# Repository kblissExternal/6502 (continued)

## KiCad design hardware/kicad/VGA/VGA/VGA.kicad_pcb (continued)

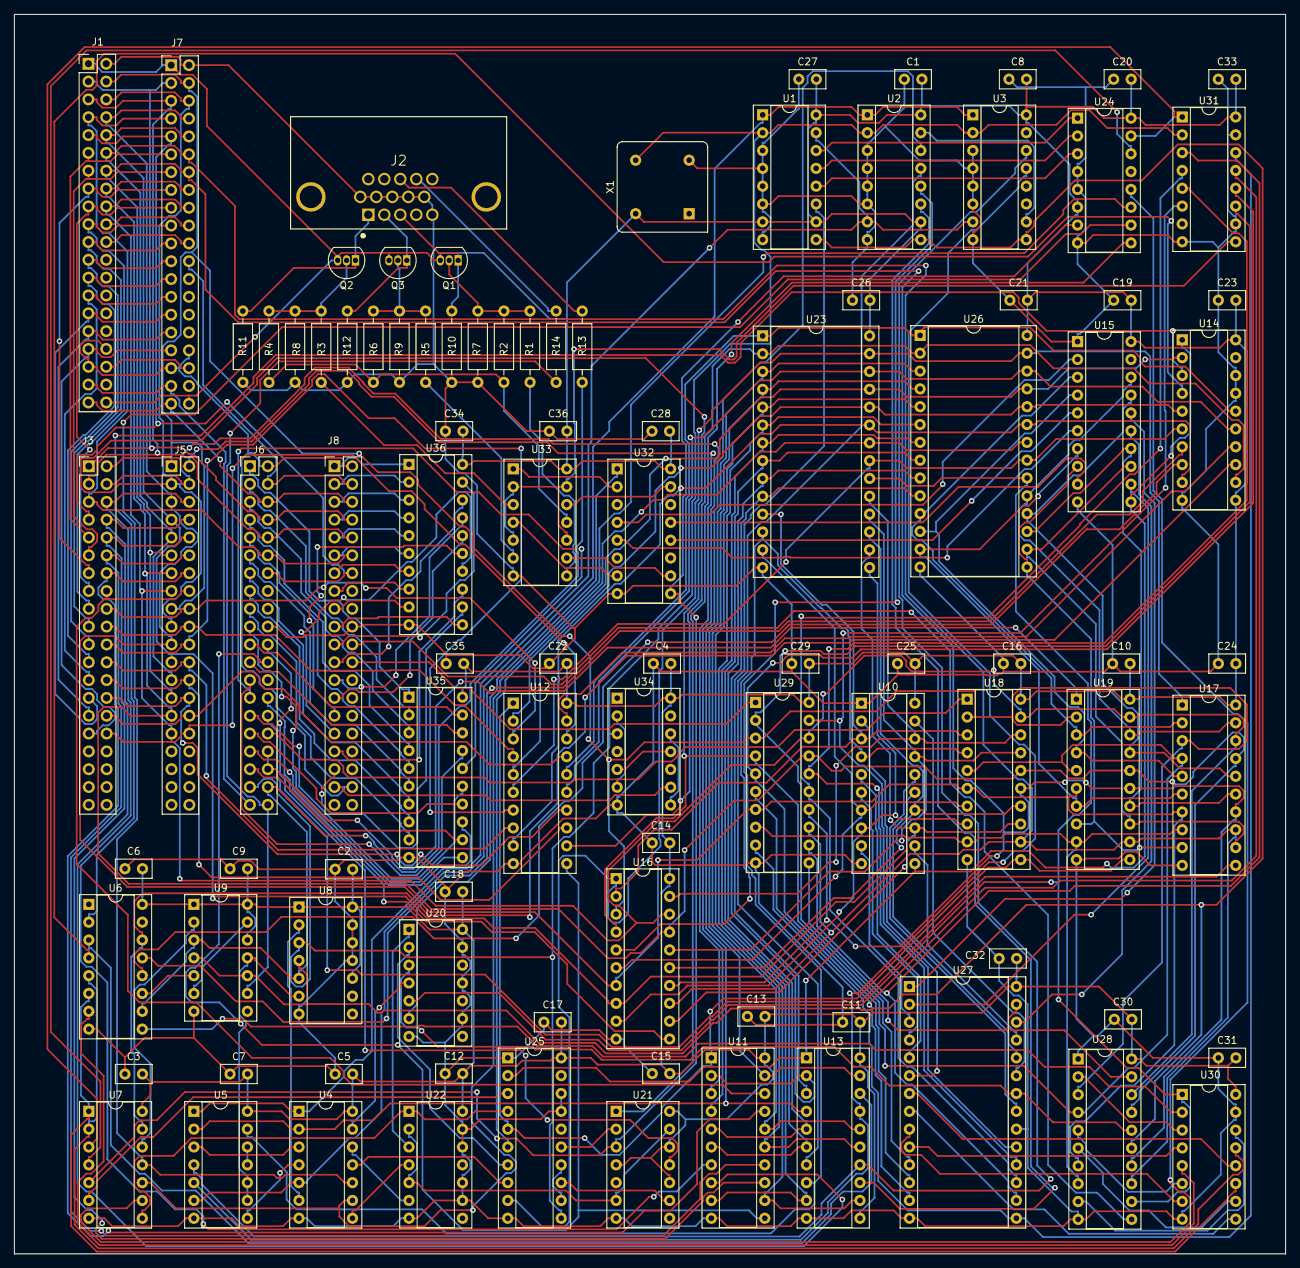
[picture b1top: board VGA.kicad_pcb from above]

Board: 2 copper layers, 181.2 x 176.6 mm, 97 parts (0 on the bottom side), 239 nets.

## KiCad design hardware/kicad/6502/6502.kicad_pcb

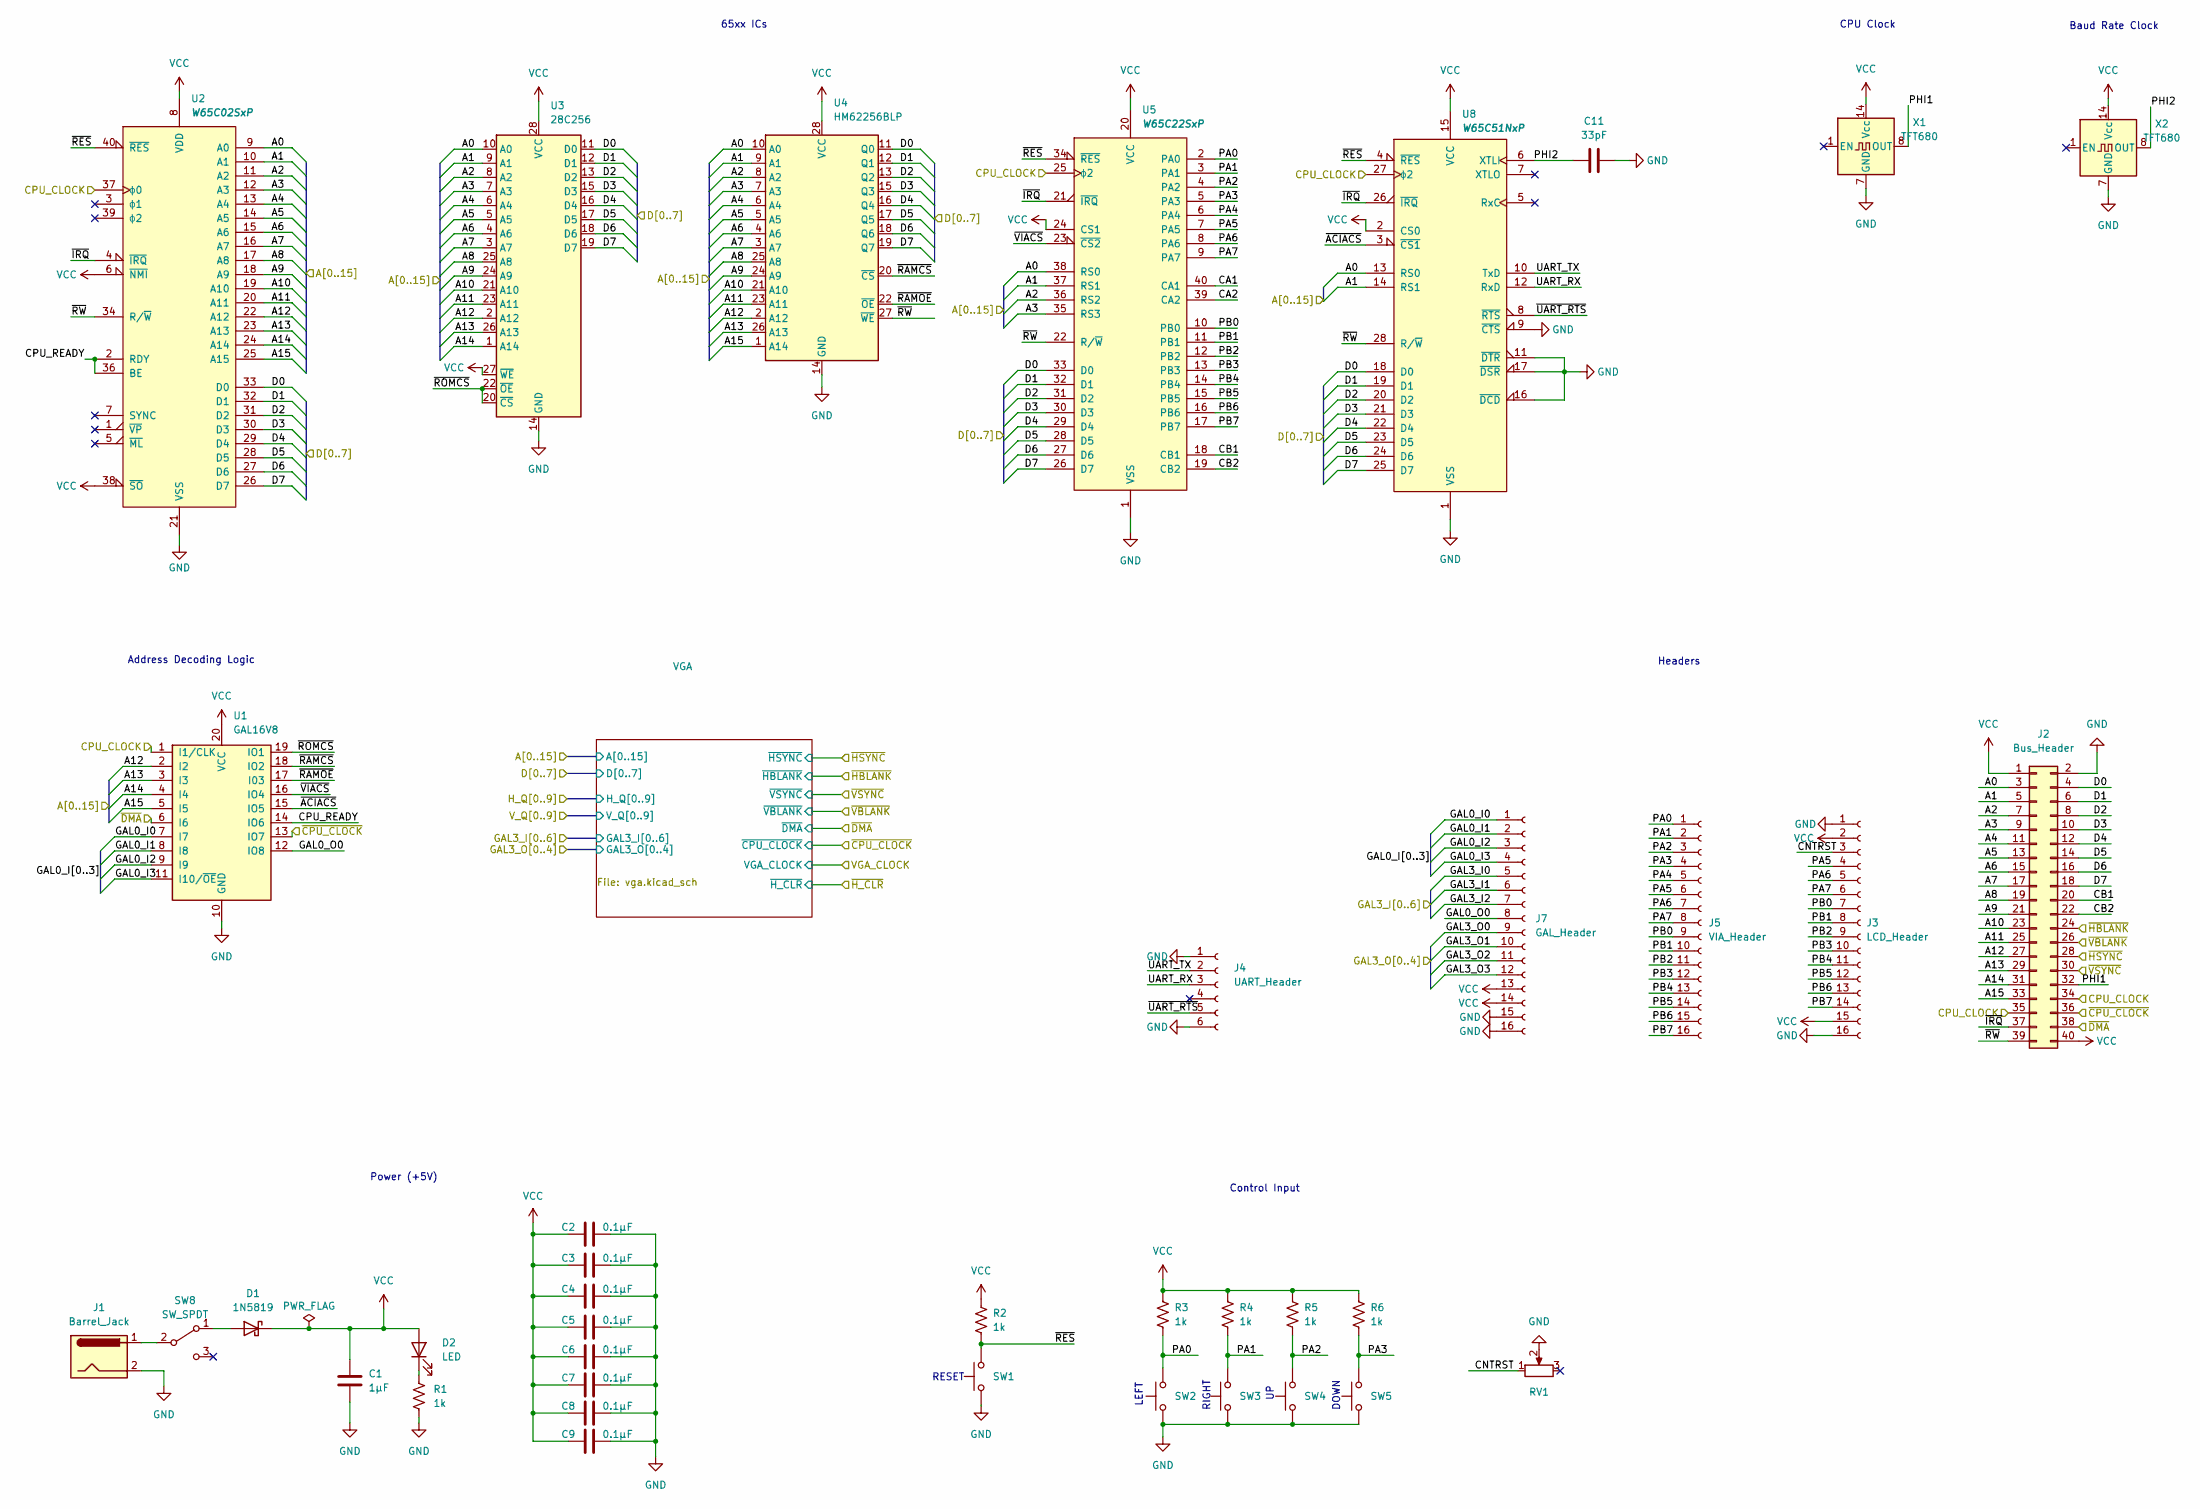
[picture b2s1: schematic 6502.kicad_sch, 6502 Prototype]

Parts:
C1: 1µF; C_Radial_D4.0mm_H5.0mm_P1.50mm
C2, C3, C4, C5, C6, C7, C8, C9: 0.1µF; C_Disc_D5.0mm_W2.5mm_P2.50mm
C11: 33pF; C_Disc_D5.0mm_W2.5mm_P5.00mm
D1: 1N5819; D_DO-41_SOD81_P10.16mm_Horizontal
D2: LED; LED_D5.0mm
J1: Barrel_Jack; BarrelJack_Horizontal
J2: Bus_Header; PinHeader_2x20_P2.54mm_Vertical
J3: LCD_Header; PinSocket_1x16_P2.54mm_Vertical
J4: UART_Header; PinSocket_1x06_P2.54mm_Vertical
J5: VIA_Header; PinSocket_1x16_P2.54mm_Vertical
J7: GAL_Header; PinSocket_1x16_P2.54mm_Vertical
R1, R2, R3, R4, R5, R6: 1k; R_Axial_DIN0207_L6.3mm_D2.5mm_P10.16mm_Horizontal
RV1: R_Potentiometer; Potentiometer_Bourns_3386C_Horizontal
SW1, SW2, SW3, SW4, SW5: SW_Push; SW_TH_Tactile_Omron_B3F-10xx
SW8: SW_SPDT; SW_THT_DPDT
U1: GAL16V8; DIP-20_W7.62mm_Socket
U2: W65C02SxP; DIP-40_W15.24mm_Socket
U3: 28C256; DIP-28_W15.24mm_Socket
U4: HM62256BLP; DIP-28_W15.24mm_Socket
U5: W65C22SxP; DIP-40_W15.24mm_Socket
U8: W65C51NxP; DIP-28_W15.24mm_Socket
X1, X2: TFT680; Oscillator_DIP-14

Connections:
/A0: J2.3, U2.9 (A0), U3.10 (A0), U4.10 (A0), U5.38 (RS0), U8.13 (RS0); also elsewhere on the board
/A1: J2.5, U2.10 (A1), U3.9 (A1), U4.9 (A1), U5.37 (RS1), U8.14 (RS1); also elsewhere on the board
/A2: J2.7, U2.11 (A2), U3.8 (A2), U4.8 (A2), U5.36 (RS2); also elsewhere on the board
/A3: J2.9, U2.12 (A3), U3.7 (A3), U4.7 (A3), U5.35 (RS3); also elsewhere on the board
/A4: J2.11, U2.13 (A4), U3.6 (A4), U4.6 (A4); also elsewhere on the board
/A5: J2.13, U2.14 (A5), U3.5 (A5), U4.5 (A5); also elsewhere on the board
/A6: J2.15, U2.15 (A6), U3.4 (A6), U4.4 (A6); also elsewhere on the board
/A7: J2.17, U2.16 (A7), U3.3 (A7), U4.3 (A7); also elsewhere on the board
/A8: J2.19, U2.17 (A8), U3.25 (A8), U4.25 (A8); also elsewhere on the board
/A9: J2.21, U2.18 (A9), U3.24 (A9), U4.24 (A9); also elsewhere on the board
/A10: J2.23, U2.19 (A10), U3.21 (A10), U4.21 (A10); also elsewhere on the board
/A11: J2.25, U2.20 (A11), U3.23 (A11), U4.23 (A11); also elsewhere on the board
/A12: J2.27, U1.2 (I2), U2.22 (A12), U3.2 (A12), U4.2 (A12); also elsewhere on the board
/A13: J2.29, U1.3 (I3), U2.23 (A13), U3.26 (A13), U4.26 (A13); also elsewhere on the board
/A14: J2.31, U1.4 (I4), U2.24 (A14), U3.1 (A14); also elsewhere on the board
/A15: J2.33, U1.5 (I5), U2.25 (A15), U4.1 (A14); also elsewhere on the board
/CA1: U5.40 (CA1)
/CA2: U5.39 (CA2)
/CB1: J2.20, U5.18 (CB1)
/CB2: J2.22, U5.19 (CB2)
/CNTRST: J3.3, RV1.1
/CPU_CLOCK: J2.34, J2.35, U1.1 (I1/CLK), U2.37 (ϕ0), U5.25 (ϕ2), U8.27 (ϕ2)
/CPU_READY: U1.14 (IO6), U2.2 (RDY), U2.36 (BE)
/D0: J2.4, U2.33 (D0), U3.11 (D0), U4.11 (Q0), U5.33 (D0), U8.18 (D0); also elsewhere on the board
/D1: J2.6, U2.32 (D1), U3.12 (D1), U4.12 (Q1), U5.32 (D1), U8.19 (D1); also elsewhere on the board
/D2: J2.8, U2.31 (D2), U3.13 (D2), U4.13 (Q2), U5.31 (D2), U8.20 (D2); also elsewhere on the board
/D3: J2.10, U2.30 (D3), U3.15 (D3), U4.15 (Q3), U5.30 (D3), U8.21 (D3); also elsewhere on the board
/D4: J2.12, U2.29 (D4), U3.16 (D4), U4.16 (Q4), U5.29 (D4), U8.22 (D4); also elsewhere on the board
/D5: J2.14, U2.28 (D5), U3.17 (D5), U4.17 (Q5), U5.28 (D5), U8.23 (D5); also elsewhere on the board
/D6: J2.16, U2.27 (D6), U3.18 (D6), U4.18 (Q6), U5.27 (D6), U8.24 (D6); also elsewhere on the board
/D7: J2.18, U2.26 (D7), U3.19 (D7), U4.19 (Q7), U5.26 (D7), U8.25 (D7); also elsewhere on the board
/GAL0_I0: J7.1, U1.7 (I7)
/GAL0_I1: J7.2, U1.8 (I8)
/GAL0_I2: J7.3, U1.9 (I9)
/GAL0_I3: J7.4, U1.11 (I10/~OE)
/GAL0_O0: J7.8, U1.12 (IO8)
/GAL3_I0: J7.5; also elsewhere on the board
/GAL3_I1: J7.6; also elsewhere on the board
/GAL3_I2: J7.7; also elsewhere on the board
/GAL3_O0: J7.9; also elsewhere on the board
/GAL3_O1: J7.10; also elsewhere on the board
/GAL3_O2: J7.11; also elsewhere on the board
/GAL3_O3: J7.12; also elsewhere on the board
/PA0: J5.1, R3.2, SW2.2, U5.2 (PA0)
/PA1: J5.2, R4.2, SW3.2, U5.3 (PA1)
/PA2: J5.3, R5.2, SW4.2, U5.4 (PA2)
/PA3: J5.4, R6.2, SW5.2, U5.5 (PA3)
/PA4: J5.5, U5.6 (PA4)
/PA5: J3.4, J5.6, U5.7 (PA5)
/PA6: J3.5, J5.7, U5.8 (PA6)
/PA7: J3.6, J5.8, U5.9 (PA7)
/PB0: J3.7, J5.9, U5.10 (PB0)
/PB1: J3.8, J5.10, U5.11 (PB1)
/PB2: J3.9, J5.11, U5.12 (PB2)
/PB3: J3.10, J5.12, U5.13 (PB3)
/PB4: J3.11, J5.13, U5.14 (PB4)
/PB5: J3.12, J5.14, U5.15 (PB5)
/PB6: J3.13, J5.15, U5.16 (PB6)
/PB7: J3.14, J5.16, U5.17 (PB7)
/PHI1: J2.32, X1.8 (OUT)
/PHI2: C11.1, U8.6 (XTLI), X2.8 (OUT)
/UART_RX: J4.3, U8.12 (RxD)
/UART_TX: J4.2, U8.10 (TxD)
/~ACIACS: U1.15 (IO5), U8.3 (~CS1)
/~CPU_CLOCK: J2.36, U1.13 (IO7); also elsewhere on the board
/~DMA: J2.38, U1.6 (I6); also elsewhere on the board
/~HBLANK: J2.24; also elsewhere on the board
/~HSYNC: J2.28; also elsewhere on the board
/~IRQ: J2.37, U2.4 (~IRQ), U5.21 (~IRQ), U8.26 (~IRQ)
/~RAMCS: U1.18 (IO2), U4.20 (~CS)
/~RAMOE: U1.17 (I03), U4.22 (~OE)
/~RES: R2.2, SW1.2, U2.40 (~RES), U5.34 (~RES), U8.4 (~RES)
/~ROMCS: U1.19 (IO1), U3.20 (~CS), U3.22 (~OE)
/~RW: J2.39, U2.34 (R/~W), U4.27 (~WE), U5.22 (R/~W), U8.28 (R/~W)
/~UART_RTS: J4.5, U8.8 (~RTS)
/~VBLANK: J2.26; also elsewhere on the board
/~VIACS: U1.16 (IO4), U5.23 (~CS2)
/~VSYNC: J2.30; also elsewhere on the board
GND: C1.2, C2.1, C3.1, C4.1, C5.1, C6.1, C7.1, C8.1, C9.1, C11.2, J1.2, J2.2, J3.1, J3.16, J4.1, J4.6, J7.15, J7.16, R1.2, RV1.2, SW1.1, SW2.1, SW3.1, SW4.1, SW5.1, U1.10 (GND), U2.21 (VSS), U3.14 (GND), U4.14 (GND), U5.1 (VSS), U8.1 (VSS), U8.9 (~CTS), U8.11 (~DTR), U8.16 (~DCD), U8.17 (~DSR), X1.7 (GND), X2.7 (GND); also elsewhere on the board
unnamed: D1.2 (A), SW8.1 (A)
unnamed: D2.1 (K), R1.1
unnamed: J1.1, SW8.2 (B)
VCC: C1.1, C2.2, C3.2, C4.2, C5.2, C6.2, C7.2, C8.2, C9.2, D1.1 (K), D2.2 (A), J2.1, J2.40, J3.2, J3.15, J7.13, J7.14, R2.1, R3.1, R4.1, R5.1, R6.1, U1.20 (VCC), U2.6 (~NMI), U2.8 (VDD), U2.38 (~SO), U3.27 (~WE), U3.28 (VCC), U4.28 (VCC), U5.20 (VCC), U5.24 (CS1), U8.2 (CS0), U8.15 (VCC), X1.14 (Vcc), X2.14 (Vcc); also elsewhere on the board

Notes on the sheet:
LEFT
Power (+5V)
Control Input
Headers
RIGHT
65xx ICs
CPU Clock
Baud Rate Clock
Address Decoding Logic
DOWN
RESET

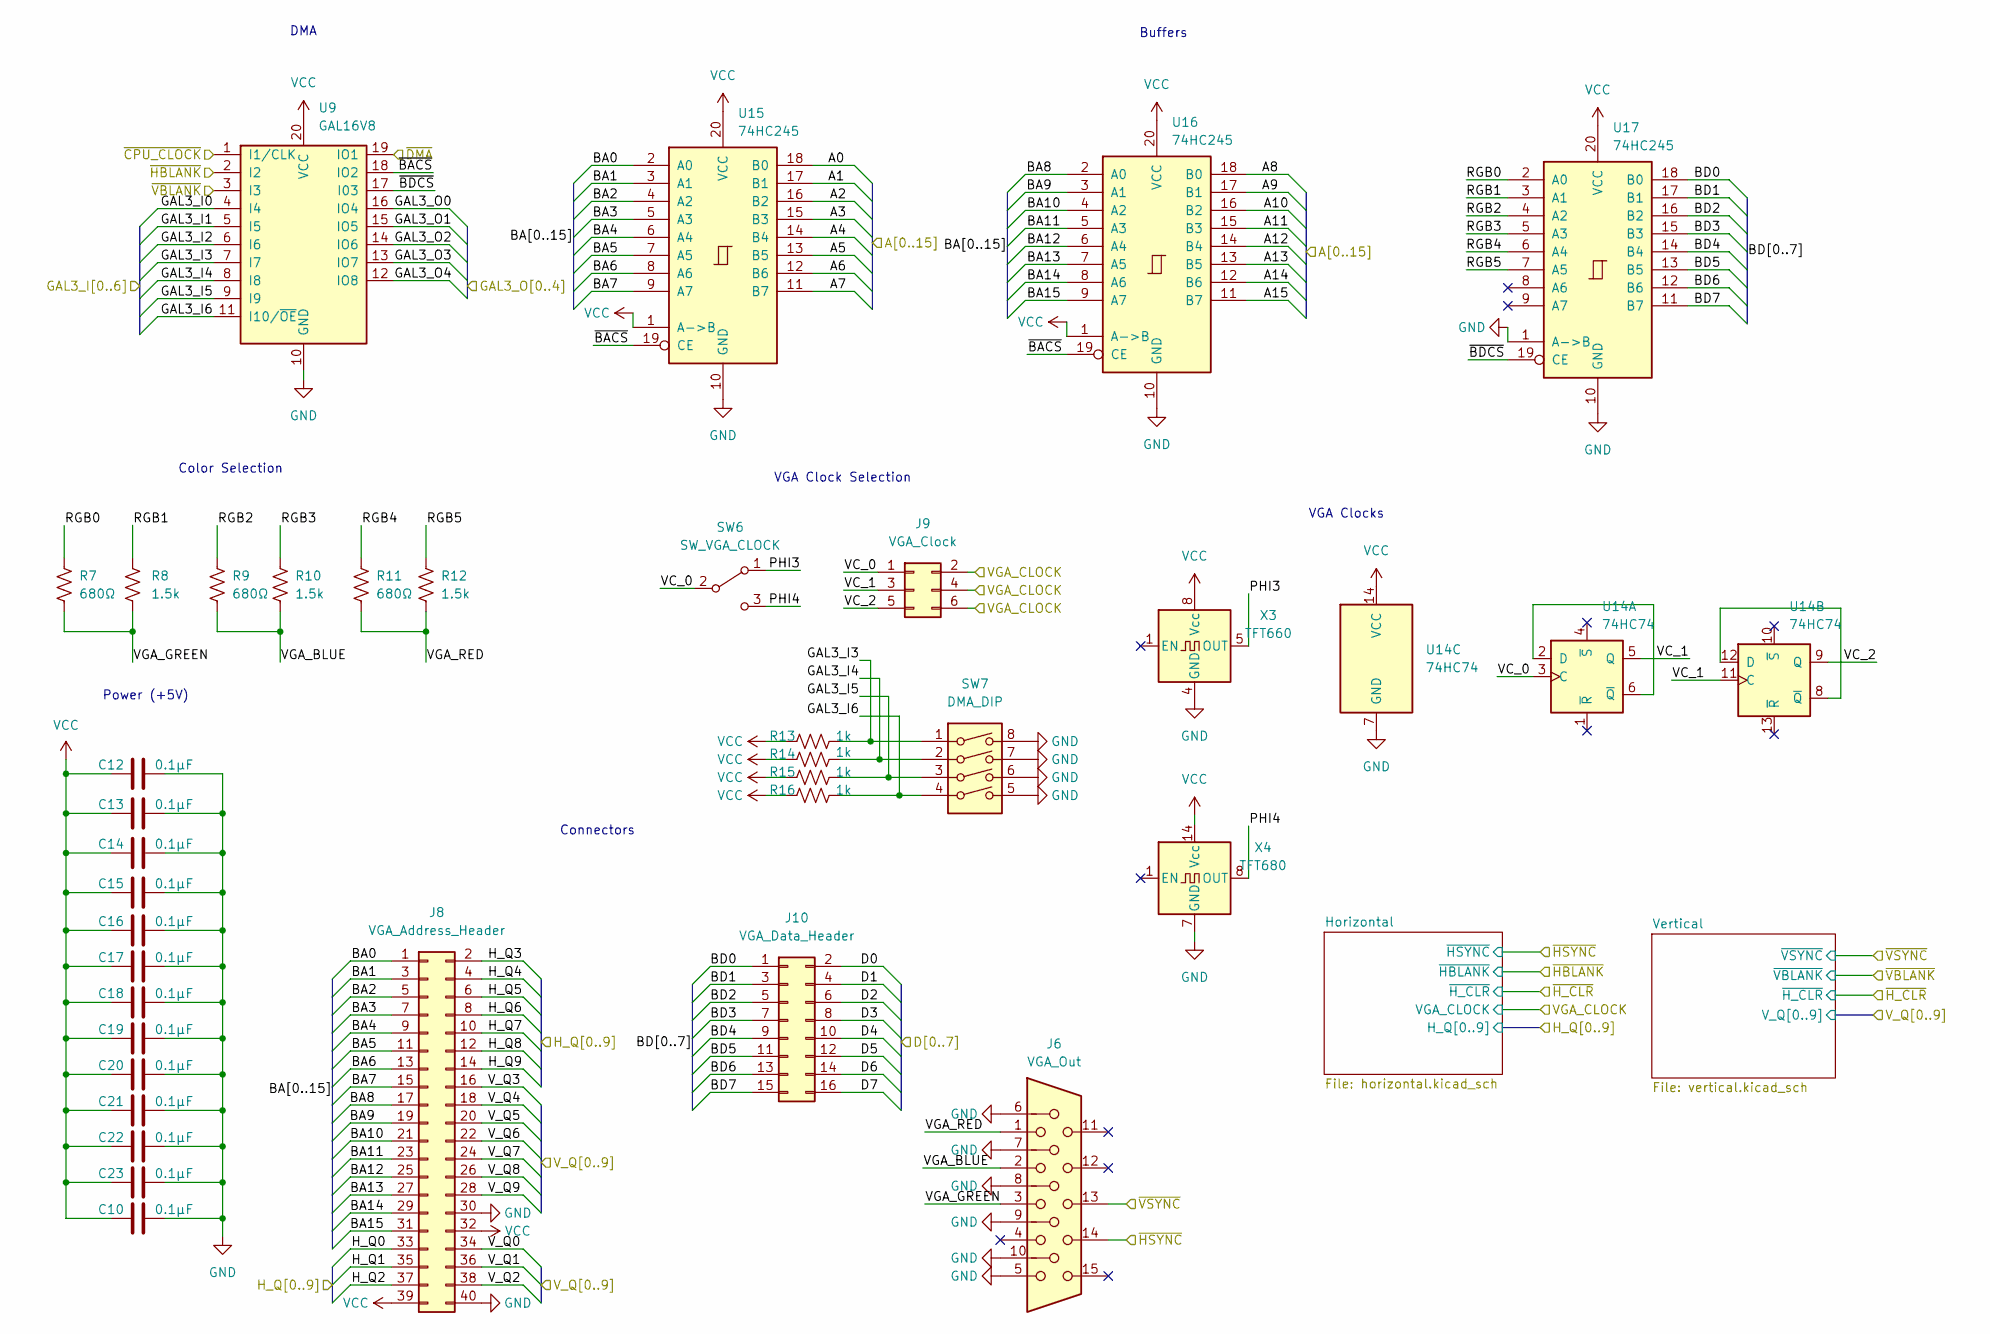
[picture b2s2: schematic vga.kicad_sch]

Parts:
C10, C12, C13, C14, C15, C16, C17, C18, C19, C20, C21, C22, C23: 0.1µF; C_Disc_D5.0mm_W2.5mm_P2.50mm
J6: VGA_Out; TE_1-1734530-1
J8: VGA_Address_Header; PinHeader_2x20_P2.54mm_Vertical
J9: VGA_Clock; PinHeader_2x03_P2.54mm_Vertical
J10: VGA_Data_Header; PinHeader_2x08_P2.54mm_Vertical
R7, R9, R11: 680Ω; R_Axial_DIN0207_L6.3mm_D2.5mm_P10.16mm_Horizontal
R8, R10, R12: 1.5k; R_Axial_DIN0207_L6.3mm_D2.5mm_P10.16mm_Horizontal
R13, R14, R15, R16: 1k; R_Axial_DIN0207_L6.3mm_D2.5mm_P10.16mm_Horizontal
SW6: SW_VGA_CLOCK; SW_THT_DPDT
SW7: DMA_DIP; SW_DIP_SPSTx04_Slide_9.78x12.34mm_W7.62mm_P2.54mm
U9: GAL16V8; DIP-20_W7.62mm_Socket
U14: 74HC74; DIP-14_W7.62mm_Socket
U15, U16, U17: 74HC245; DIP-20_W7.62mm_Socket
X3: TFT660; Oscillator_DIP-8
X4: TFT680; Oscillator_DIP-14

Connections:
/A0: U15.18 (B0); also elsewhere on the board
/A1: U15.17 (B1); also elsewhere on the board
/A2: U15.16 (B2); also elsewhere on the board
/A3: U15.15 (B3); also elsewhere on the board
/A4: U15.14 (B4); also elsewhere on the board
/A5: U15.13 (B5); also elsewhere on the board
/A6: U15.12 (B6); also elsewhere on the board
/A7: U15.11 (B7); also elsewhere on the board
/A8: U16.18 (B0); also elsewhere on the board
/A9: U16.17 (B1); also elsewhere on the board
/A10: U16.16 (B2); also elsewhere on the board
/A11: U16.15 (B3); also elsewhere on the board
/A12: U16.14 (B4); also elsewhere on the board
/A13: U16.13 (B5); also elsewhere on the board
/A14: U16.12 (B6); also elsewhere on the board
/A15: U16.11 (B7); also elsewhere on the board
/D0: J10.2; also elsewhere on the board
/D1: J10.4; also elsewhere on the board
/D2: J10.6; also elsewhere on the board
/D3: J10.8; also elsewhere on the board
/D4: J10.10; also elsewhere on the board
/D5: J10.12; also elsewhere on the board
/D6: J10.14; also elsewhere on the board
/D7: J10.16; also elsewhere on the board
/GAL3_I0: U9.4 (I4); also elsewhere on the board
/GAL3_I1: U9.5 (I5); also elsewhere on the board
/GAL3_I2: U9.6 (I6); also elsewhere on the board
/GAL3_I3: R13.2, SW7.1, U9.7 (I7)
/GAL3_I4: R14.2, SW7.2, U9.8 (I8)
/GAL3_I5: R15.2, SW7.3, U9.9 (I9)
/GAL3_I6: R16.2, SW7.4, U9.11 (I10/~OE)
/GAL3_O0: U9.16 (IO4); also elsewhere on the board
/GAL3_O1: U9.15 (IO5); also elsewhere on the board
/GAL3_O2: U9.14 (IO6); also elsewhere on the board
/GAL3_O3: U9.13 (IO7); also elsewhere on the board
/GAL3_O4: U9.12 (IO8)
/H_Q0: J8.33; also elsewhere on the board
/H_Q1: J8.35; also elsewhere on the board
/H_Q2: J8.37; also elsewhere on the board
/H_Q3: J8.2; also elsewhere on the board
/H_Q4: J8.4; also elsewhere on the board
/H_Q5: J8.6; also elsewhere on the board
/H_Q6: J8.8; also elsewhere on the board
/H_Q7: J8.10; also elsewhere on the board
/H_Q8: J8.12; also elsewhere on the board
/H_Q9: J8.14; also elsewhere on the board
/VGA/BA0: J8.1, U15.2 (A0)
/VGA/BA1: J8.3, U15.3 (A1)
/VGA/BA2: J8.5, U15.4 (A2)
/VGA/BA3: J8.7, U15.5 (A3)
/VGA/BA4: J8.9, U15.6 (A4)
/VGA/BA5: J8.11, U15.7 (A5)
/VGA/BA6: J8.13, U15.8 (A6)
/VGA/BA7: J8.15, U15.9 (A7)
/VGA/BA8: J8.17, U16.2 (A0)
/VGA/BA9: J8.19, U16.3 (A1)
/VGA/BA10: J8.21, U16.4 (A2)
/VGA/BA11: J8.23, U16.5 (A3)
/VGA/BA12: J8.25, U16.6 (A4)
/VGA/BA13: J8.27, U16.7 (A5)
/VGA/BA14: J8.29, U16.8 (A6)
/VGA/BA15: J8.31, U16.9 (A7)
/VGA/BD0: J10.1, U17.18 (B0)
/VGA/BD1: J10.3, U17.17 (B1)
/VGA/BD2: J10.5, U17.16 (B2)
/VGA/BD3: J10.7, U17.15 (B3)
/VGA/BD4: J10.9, U17.14 (B4)
/VGA/BD5: J10.11, U17.13 (B5)
/VGA/BD6: J10.13, U17.12 (B6)
/VGA/BD7: J10.15, U17.11 (B7)
/VGA/PHI3: SW6.1 (A), X3.5 (OUT)
/VGA/PHI4: SW6.3 (C), X4.8 (OUT)
/VGA/RGB0: R7.1, U17.2 (A0)
/VGA/RGB1: R8.2, U17.3 (A1)
/VGA/RGB2: R9.1, U17.4 (A2)
/VGA/RGB3: R10.1, U17.5 (A3)
/VGA/RGB4: R11.1, U17.6 (A4)
/VGA/RGB5: R12.1, U17.7 (A5)
/VGA/VC_0: J9.1, SW6.2 (B), U14.3 (C)
/VGA/VC_1: J9.3, U14.5 (Q), U14.11 (C)
/VGA/VC_2: J9.5, U14.9 (Q)
/VGA/VGA_BLUE: J6.2, R9.2, R10.2
/VGA/VGA_GREEN: J6.3, R7.2, R8.1
/VGA/VGA_RED: J6.1, R11.2, R12.2
/VGA/~BACS: U9.18 (IO2), U15.19 (CE), U16.19 (CE)
/VGA/~BDCS: U9.17 (I03), U17.19 (CE)
/VGA_CLOCK: J9.2, J9.4, J9.6; also elsewhere on the board
/V_Q0: J8.34; also elsewhere on the board
/V_Q1: J8.36; also elsewhere on the board
/V_Q2: J8.38; also elsewhere on the board
/V_Q3: J8.16; also elsewhere on the board
/V_Q4: J8.18; also elsewhere on the board
/V_Q5: J8.20; also elsewhere on the board
/V_Q6: J8.22; also elsewhere on the board
/V_Q7: J8.24; also elsewhere on the board
/V_Q8: J8.26; also elsewhere on the board
/V_Q9: J8.28; also elsewhere on the board
/~CPU_CLOCK: U9.1 (I1/CLK); also elsewhere on the board
/~DMA: U9.19 (IO1); also elsewhere on the board
/~HBLANK: U9.2 (I2); also elsewhere on the board
/~HSYNC: J6.14; also elsewhere on the board
/~VBLANK: U9.3 (I3); also elsewhere on the board
/~VSYNC: J6.13; also elsewhere on the board
GND: C10.1, C12.1, C13.1, C14.1, C15.1, C16.1, C17.1, C18.1, C19.1, C20.1, C21.1, C22.1, C23.1, J6.5, J6.6, J6.7, J6.8, J6.9, J6.10, J8.30, J8.40, SW7.5, SW7.6, SW7.7, SW7.8, U9.10 (GND), U14.7 (GND), U15.10 (GND), U16.10 (GND), U17.1 (A->B), U17.10 (GND), X3.4 (GND), X4.7 (GND); also elsewhere on the board
unnamed: U14.2 (D), U14.6 (~Q)
unnamed: U14.8 (~Q), U14.12 (D)
VCC: C10.2, C12.2, C13.2, C14.2, C15.2, C16.2, C17.2, C18.2, C19.2, C20.2, C21.2, C22.2, C23.2, J8.32, J8.39, R13.1, R14.1, R15.1, R16.1, U9.20 (VCC), U14.14 (VCC), U15.1 (A->B), U15.20 (VCC), U16.1 (A->B), U16.20 (VCC), U17.20 (VCC), X3.8 (Vcc), X4.14 (Vcc); also elsewhere on the board

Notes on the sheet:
Buffers
VGA Clocks
DMA
VGA Clock Selection
Connectors
Color Selection
Power (+5V)

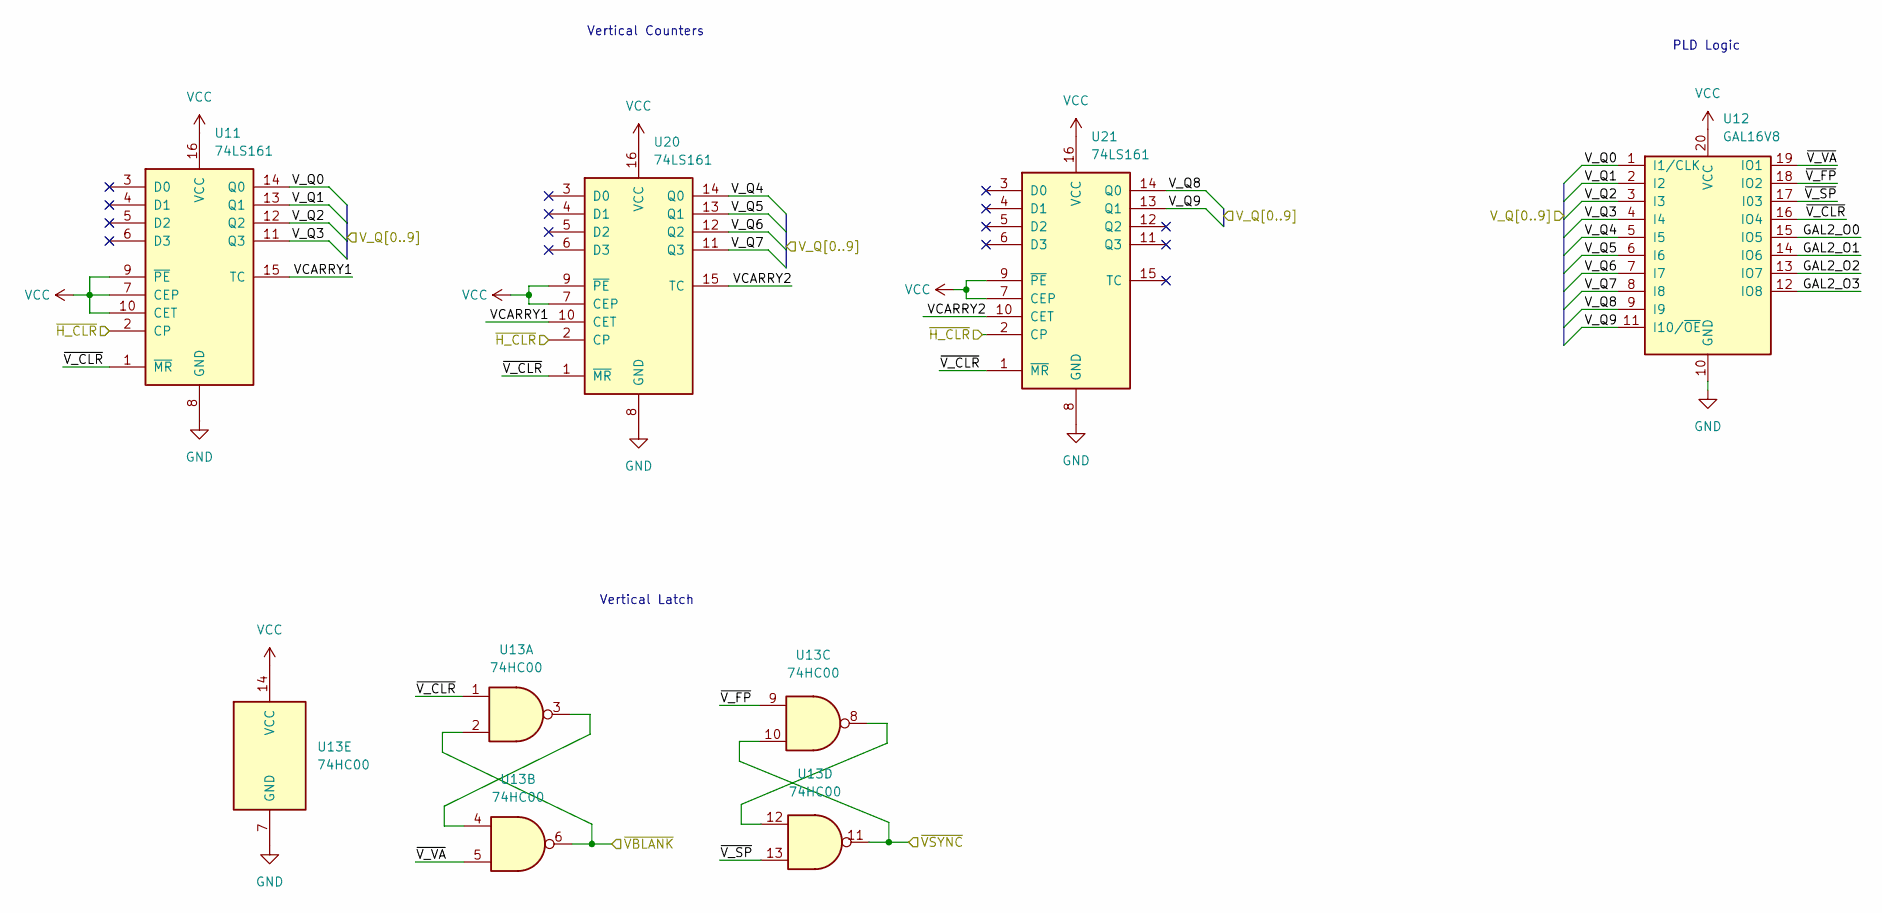
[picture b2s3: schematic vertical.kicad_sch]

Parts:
U11, U20, U21: 74LS161; DIP-16_W7.62mm_Socket
U12: GAL16V8; DIP-20_W7.62mm_Socket
U13: 74HC00; DIP-14_W7.62mm_Socket

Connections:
/VGA/Horizontal/~H_CLR: U11.2 (CP), U20.2 (CP), U21.2 (CP); also elsewhere on the board
/VGA/Vertical/GAL2_O0: U12.15 (IO5)
/VGA/Vertical/GAL2_O1: U12.14 (IO6)
/VGA/Vertical/GAL2_O2: U12.13 (IO7)
/VGA/Vertical/GAL2_O3: U12.12 (IO8)
/VGA/Vertical/VCARRY1: U11.15 (TC), U20.10 (CET)
/VGA/Vertical/VCARRY2: U20.15 (TC), U21.10 (CET)
/VGA/Vertical/~V_CLR: U11.1 (~MR), U12.16 (IO4), U13.1, U20.1 (~MR), U21.1 (~MR)
/VGA/Vertical/~V_FP: U12.18 (IO2), U13.9
/VGA/Vertical/~V_SP: U12.17 (I03), U13.13
/VGA/Vertical/~V_VA: U12.19 (IO1), U13.5
/V_Q0: U11.14 (Q0), U12.1 (I1/CLK); also elsewhere on the board
/V_Q1: U11.13 (Q1), U12.2 (I2); also elsewhere on the board
/V_Q2: U11.12 (Q2), U12.3 (I3); also elsewhere on the board
/V_Q3: U11.11 (Q3), U12.4 (I4); also elsewhere on the board
/V_Q4: U12.5 (I5), U20.14 (Q0); also elsewhere on the board
/V_Q5: U12.6 (I6), U20.13 (Q1); also elsewhere on the board
/V_Q6: U12.7 (I7), U20.12 (Q2); also elsewhere on the board
/V_Q7: U12.8 (I8), U20.11 (Q3); also elsewhere on the board
/V_Q8: U12.9 (I9), U21.14 (Q0); also elsewhere on the board
/V_Q9: U12.11 (I10/~OE), U21.13 (Q1); also elsewhere on the board
/~VBLANK: U13.2, U13.6; also elsewhere on the board
/~VSYNC: U13.10, U13.11; also elsewhere on the board
GND: U11.8 (GND), U12.10 (GND), U13.7 (GND), U20.8 (GND), U21.8 (GND); also elsewhere on the board
unnamed: U13.3, U13.4
unnamed: U13.8, U13.12
VCC: U11.7 (CEP), U11.9 (~PE), U11.10 (CET), U11.16 (VCC), U12.20 (VCC), U13.14 (VCC), U20.7 (CEP), U20.9 (~PE), U20.16 (VCC), U21.7 (CEP), U21.9 (~PE), U21.16 (VCC); also elsewhere on the board

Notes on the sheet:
PLD Logic
Vertical Counters
Vertical Latch

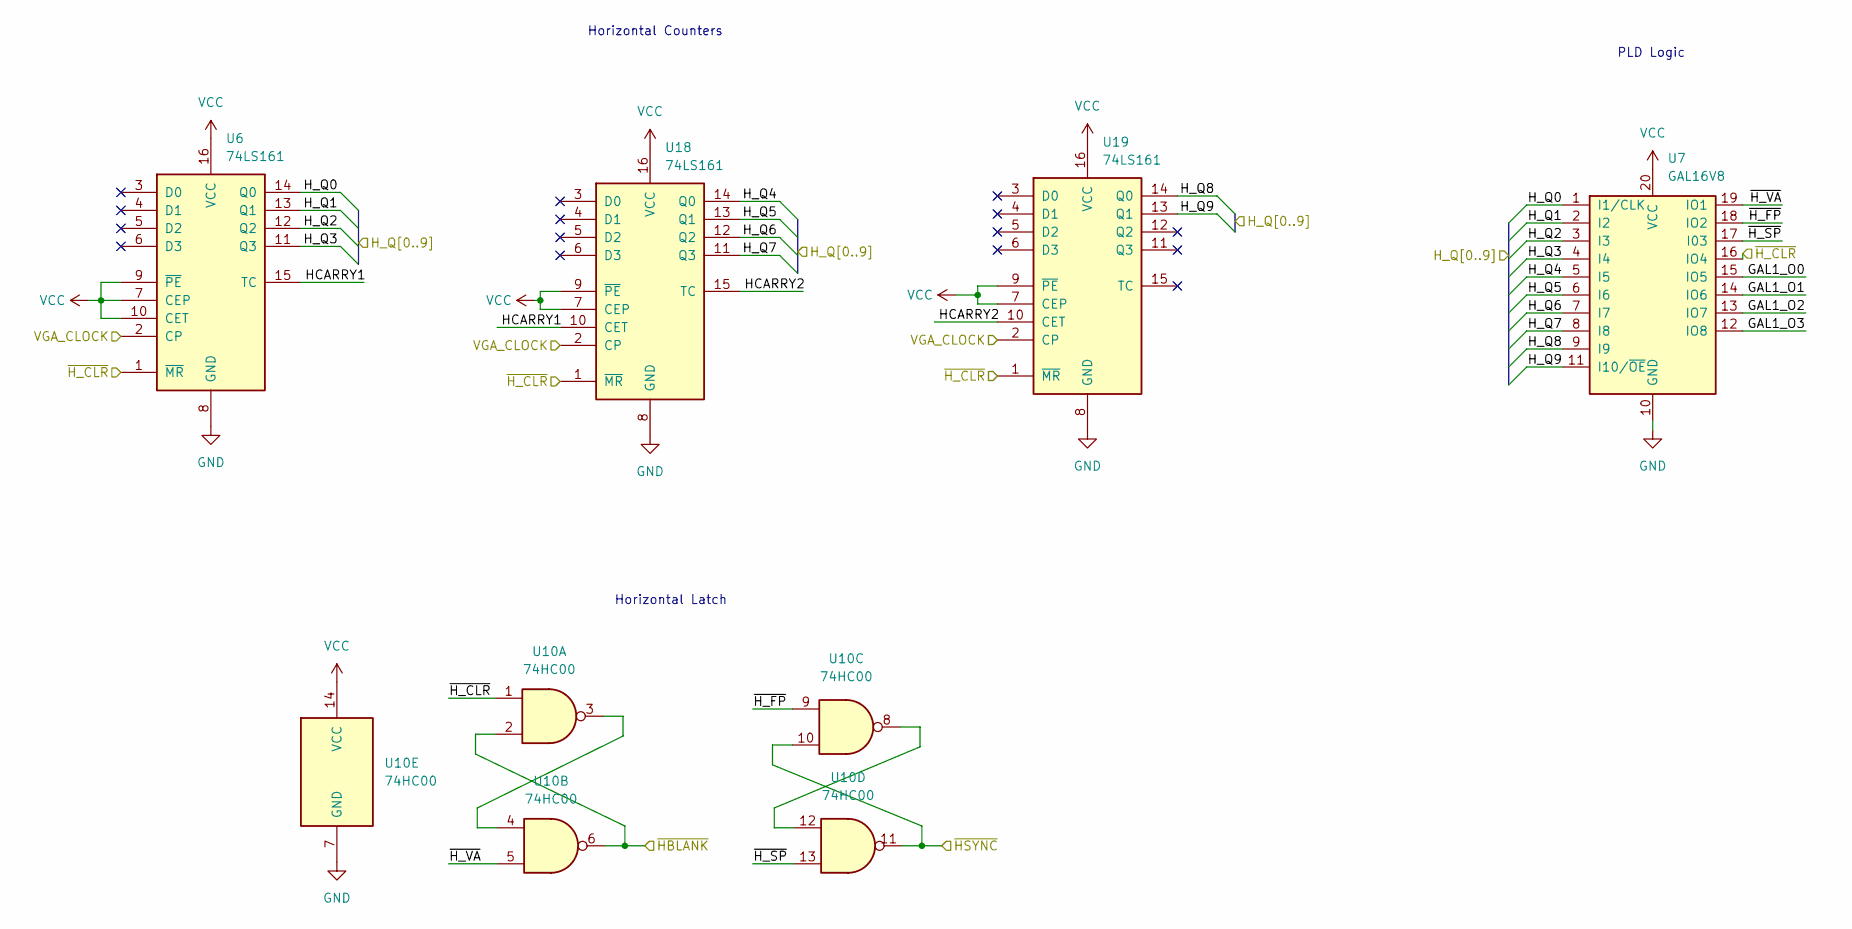
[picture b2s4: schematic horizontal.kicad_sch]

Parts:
U6, U18, U19: 74LS161; DIP-16_W7.62mm_Socket
U7: GAL16V8; DIP-20_W7.62mm_Socket
U10: 74HC00; DIP-14_W7.62mm_Socket

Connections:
/H_Q0: U6.14 (Q0), U7.1 (I1/CLK); also elsewhere on the board
/H_Q1: U6.13 (Q1), U7.2 (I2); also elsewhere on the board
/H_Q2: U6.12 (Q2), U7.3 (I3); also elsewhere on the board
/H_Q3: U6.11 (Q3), U7.4 (I4); also elsewhere on the board
/H_Q4: U7.5 (I5), U18.14 (Q0); also elsewhere on the board
/H_Q5: U7.6 (I6), U18.13 (Q1); also elsewhere on the board
/H_Q6: U7.7 (I7), U18.12 (Q2); also elsewhere on the board
/H_Q7: U7.8 (I8), U18.11 (Q3); also elsewhere on the board
/H_Q8: U7.9 (I9), U19.14 (Q0); also elsewhere on the board
/H_Q9: U7.11 (I10/~OE), U19.13 (Q1); also elsewhere on the board
/VGA/Horizontal/GAL1_O0: U7.15 (IO5)
/VGA/Horizontal/GAL1_O1: U7.14 (IO6)
/VGA/Horizontal/GAL1_O2: U7.13 (IO7)
/VGA/Horizontal/GAL1_O3: U7.12 (IO8)
/VGA/Horizontal/HCARRY1: U6.15 (TC), U18.10 (CET)
/VGA/Horizontal/HCARRY2: U18.15 (TC), U19.10 (CET)
/VGA/Horizontal/~H_CLR: U6.1 (~MR), U7.16 (IO4), U10.1, U18.1 (~MR), U19.1 (~MR); also elsewhere on the board
/VGA/Horizontal/~H_FP: U7.18 (IO2), U10.9
/VGA/Horizontal/~H_SP: U7.17 (I03), U10.13
/VGA/Horizontal/~H_VA: U7.19 (IO1), U10.5
/VGA_CLOCK: U6.2 (CP), U18.2 (CP), U19.2 (CP); also elsewhere on the board
/~HBLANK: U10.2, U10.6; also elsewhere on the board
/~HSYNC: U10.10, U10.11; also elsewhere on the board
GND: U6.8 (GND), U7.10 (GND), U10.7 (GND), U18.8 (GND), U19.8 (GND); also elsewhere on the board
unnamed: U10.3, U10.4
unnamed: U10.8, U10.12
VCC: U6.7 (CEP), U6.9 (~PE), U6.10 (CET), U6.16 (VCC), U7.20 (VCC), U10.14 (VCC), U18.7 (CEP), U18.9 (~PE), U18.16 (VCC), U19.7 (CEP), U19.9 (~PE), U19.16 (VCC); also elsewhere on the board

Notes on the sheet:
Horizontal Latch
Horizontal Counters
PLD Logic
